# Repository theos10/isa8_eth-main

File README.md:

# ISA 8-Bit Ethernet Controller Low Profile
ISA 8-Bit Ethernet Network Interface Controller

## Introduction
ISA 8-Bit Ethernet Controller is an open source network interface controller (NIC) card, designed specifically to be used in computers with 8-bit only ISA (aka XT) bus, such as IBM* PC, IBM* PC XT, various PC/XT compatibles, for example [Micro 8088](https://github.com/skiselev/micro_8088) system. It is based on Realtek RTL8019 ethernet controller and is NE2000-compatible.

## Revision
Upgrade of the PCP to Low Profile by FOURNIER Ghislain.
Allows the card to be used in an Olivetti M19.
* Removal of the memory expansion connector MEM_EXT.
* Removal of the EPROM holder.
* Removal of the ROM address selection switches SW4.
* Removal and replacement of the RN3 and RN4 resistor network with an R4 SMD resistor.

## Specifications
* ISA 8-bit interface (62 pin / card edge)
* NE2000 compatible
  * Note: Popular Crynwr NE2000 pocket driver does not support NE2000 in 8-bit slots. Please use the [patched driver](software/driver/) instead
* Supports configuration using switches, jumperless configuration using [RSET8019](software/RSET8019/) utility or PnP
  * Uses DIP switches instead of jumpers for reliability and ease of configuration
* Boot ROM support
  * Socket supports 512 KiB Flash ROM, such as SST/Microchip 39SF040
  * Can be configured in 16 KiB, 32 KiB, 64 KiB, or page mode. In page mode the entire 512 KiB are accessible through a 16 KiB window
  * Also compatible with other DIP 32-pin Flash ROMs, such as 128 KiB 39SF010A, and 256 KiB 39SF020, or similar
  * 40-pin memory extension connector allows connecting up to 4 MiB of memory that can be used in page mode

## Hardware Documentation

### Schematic and PCB Layout

[Schematic - Version 1.0](KiCad/ISA8_Ethernet-Schematic-1.0.pdf)

[PCB Layout - Version 1.0](KiCad/ISA8_Ethernet-Board-1.0.pdf)

### Building Instructions

#### Assemble the PCB

* Clean the PCB with alcohol
* Apply fluid flux to SMD components pads
* Solder U1 RTL8019 IC
* Solder R1 - R7 resistors and RN1 - RN4 resistor arrays
  * Note that RN1 - RN3 are only required if using DIP switches for configuration. They are not required for jumperless configuration
* Solder C1 - C8 ceramic capacitors
* Solder C9 and C10 tantalum capacitors
* Solder Y1 crystal
* Optional: Program U3 EEPROM. Make sure to use unique MAC address
  * Note: EEPROM can be programmed later using [PG8019](software/PG8019/) utility
* Solder U3 EEPROM
* Optional: Solder SW1 - SW4 DIP switches and U2 IC socket
* Solder J1 Ethernet jack with integrated magentics
* Clean the remaining flux with alcohol

#### Program EEPROM

If EEPROM has not been programmed prior to assembly, now it is a good time to do so.
The U3 EEPROM contains the following configuration for the RTL8019AS chip:
* MAC address
* ISA resources for jumperless configuration
  * Base I/O address
  * IRQ number
  * Boot ROM mode, size, and base memory address
* Other ethernet controller confirguration - medium type, full duplex, LEDs function, power management settings
* Product ID (not normally used, although some vendor specific drivers might check for it)
* Plug and Play data
  * Vendor ID, serial number, PnP version, I/O, memory, and IRQ resources

This information can be programmed using [PG8019](software/PG8019/) utility. The 8019AS.CFG file contains the recommended configuration. Make sure to edit it, and update the MAC address and the serial number. Note that the MAC address is given in the Big-endian format (that is the last byte has the least significant value), while the serial number is given in Little-endian format (that is the first byte has the least significant value). 

A few notes about using PG8019:
* Make sure that your system has 0x300-0x31F I/O addresses available regardless of the Ethernet controller addresses specified in 8019AS.CFG. Note that XT-IDE and XT-CF-Lite frequently use this I/O range. In case you have such a card, you can either temporarily remove it from your system, boot and run PG8019 from a floppy disk, or switch your XT-IDE or XT-CF-Lite to a different address. In the latter case you'll need to update the XT IDE BIOS configuration
* Make sure that your system boots in real mode (no EMM386), or anything else that might interfer with the card. Ideally boot your system without any drivers loaded at all, for example, in later MS-DOS versions it is possible to bypass CONFIG.SYS and AUTOEXEC.BAT by hitting F5 key at the boot time
* After EEPROM has been programmed successfully, the PG8019 utility will print the MAC address, also, it will automatically increment the MAC address and the serial number in 8019AS.CFG, which is useful when programming multiple cards

[Openmoko Inc.](https://github.com/skiselev/openmoko-usb-oui) has generously allocated [00-1F-11-02-60-00 - 00-1F-11-02-7F-FF](https://github.com/skiselev/openmoko-usb-oui/blob/master/ieee_oui.psv) MAC addresses range for ISA 8-Bit Ethernet controller project. You can use MAC addresses from this range for your build, as long as you are using this design. Please apply for a different range if you're redesigning the board or re-using this Ethernet controller design in your own project. I ask you not to use 00-1F-11-02-60-00 - 00-1F-11-02-63-FF range (first 1024 addresses). I am using this range for the cards that I build.

#### Test Ethernet Controller

* Connect Ethernet cable. Make sure that the green "Link" LED lights up
* Use mTCP to test the controller
  * DHCP to obtain IP address
  * FTP or HTGET to download a file

### Switches and Connectors

#### SW1 - CONFIG
This switch block sets the configuration mode

Configuration Mode    | Switch Position
--------------------- | ------------------------
Jumperless / RSET8019 | SW1.1 = OFF, SW1.2 = OFF
Switches              | SW1.1 = ON, SW1.2 = OFF
PnP                   | SW1.1 = OFF, SW1.2 = ON

#### SW2 - IRQ
This switch block, when the card is in the **Switches** configuration mode, sets the Ethernet controller IRQ

IRQ                             | Switch Position
------------------------------- | ------------------------
IRQ2 (on PC/XT) or IRQ9 (on AT) | SW2.1 = OFF, SW2.2 = OFF
IRQ3                            | SW2.1 = ON, SW2.2 = OFF
IRQ4                            | SW2.1 = OFF, SW2.2 = ON
IRQ5                            | SW2.1 = ON, SW2.2 = ON

#### SW3 - IO_ADDR
This switch block, when the card is in the **Switches** configuration mode, sets the Ethernet controller I/O address

I/O Address | SW3.1 | SW3.2 | SW3.3 | SW3.4
----------- | ----- | ----- | ------| -----
0x200       | OFF   | OFF   | ON    | OFF
0x220       | ON    | OFF   | ON    | OFF
0x240       | OFF   | ON    | ON    | OFF
0x260       | ON    | ON    | ON    | OFF
0x280       | OFF   | OFF   | ON    | ON
0x2A0       | ON    | OFF   | ON    | ON
0x2C0       | OFF   | ON    | ON    | ON
0x2E0       | ON    | ON    | ON    | ON
0x300       | OFF   | OFF   | OFF   | OFF
0x320       | ON    | OFF   | OFF   | OFF
0x340       | OFF   | ON    | OFF   | OFF
0x360       | ON    | ON    | OFF   | OFF
0x380       | OFF   | OFF   | OFF   | ON
0x3A0       | ON    | OFF   | OFF   | ON
0x3C0       | OFF   | ON    | OFF   | ON
0x3E0       | ON    | ON    | OFF   | ON

#### J1 - Ethernet Connector

### Bill of Materials - Version 1.0

[ISA 8-bit Ethernet project on Mouser.com](https://www.mouser.com/ProjectManager/ProjectDetail.aspx?AccessID=6373f65c4a) - View and order all components except of the PCB and the Realtek RTL8019 IC.

[ISA 8-bit Ethernet project on OSH Park](https://oshpark.com/shared_projects/OBud8i6u) - View and order the PCB.

Component type     | Reference | Description                           | Quantity | Possible sources and notes 
------------------ | --------- | ------------------------------------- | -------- | --------------------------
PCB                |           | ISA 8-bit Ethernet PCB - Version 1.0  | 1        | Buy from my Tindie store: [ISA 8-bit Ethernet PCB, and optionally a preprogrammed EEPROM](https://www.tindie.com/products/weird/isa8-eth-pcb), or order from a PCB manufacturer of your choice using provided Gerber or KiCad files
Integrated Circuit | U1        | Realtek RTL8019AS Ethernet Controller | 1        | Authorized Realtek distributors or eBay
Integrated Circuit | U3        | 93C46 - 1 Kbit EEPROM, 4 pin SOIC     | 1        | Mouser [511-M93C46-WMN6TP](https://www.mouser.com/ProductDetail/511-M93C46-WMN6TP)
Quartz Crystal     | Y1        | 20 MHz, 18pF, HC-49U                  | 1        | Mouser [774-ATS200C](https://www.mouser.com/ProductDetail/774-ATS200C)
Ethernet Jack      | J1        | Amphenol RJMG1BD3B8K1ANR - Ethernet jack with magnetics | 1 | Mouser [523-RJMG1BD3B8K1ANR](https://www.mouser.com/ProductDetail/523-RJMG1BD3B8K1ANR)
DIP Switch         | SW1, SW2  | DIP switch, 2 position, SPST          | 2        | Mouser [774-2102MS](https://www.mouser.com/ProductDetail/774-2102MS)
DIP Switch         | SW3       | DIP switch, 4 position, SPST          | 1        | Mouser [774-2104MS](https://www.mouser.com/ProductDetail/774-2104MS)
Capacitor          | C1, C2    | 10pF MLCC Capacitor, 0603 SMT         | 2        | Mouser [77-VJ0603A100JXACBC](https://www.mouser.com/ProductDetail/77-VJ0603A100JXACBC)
Capacitor          | C3, C4    | 0.01uF MLCC Capacitor, 0603 SMT       | 2        | Mouser [77-VJ0603Y103JXACBC](https://www.mouser.com/ProductDetail/77-VJ0603Y103JXACBC)
Capacitor          | C5 - C8   | 0.1uF MLCC Capacitor, 0603 SMT        | 4        | Mouser [77-VJ0603Y104JXJPBC](https://www.mouser.com/ProductDetail/77-VJ0603Y104JXJPBC)
Capacitor          | C9, C10   | 22uF Tantalum Capacitor, 1210 SMT     | 2        | Mouser [581-TAJB226K016TNJ](https://www.mouser.com/ProductDetail/581-TAJB226K016TNJ)
Resistor           | R1        | 200 Ohm Resistor, 0603 SMT            | 1        | Mouser [603-RC0603FR-13200RL](https://www.mouser.com/ProductDetail/603-RC0603FR-13200RL)
Resistor           | R2, R3    | 470 Ohm Resistor, 0603 SMT            | 2        | Mouser [603-RC0603FR-13470RL](https://www.mouser.com/ProductDetail/603-RC0603FR-13470RL)
Resistor           | R4        | 10 kOhm Resistor, 0603 SMT            | 1        | Mouser [603-RC0603FR-1310KL](https://www.mouser.fr/ProductDetail/YAGEO/RC0603FR-1310KL)
Resistor           | R6        | 27 kOhm Resistor, 0603 SMT            | 1        | Mouser [603-RC0603FR-1327KL](https://www.mouser.com/ProductDetail/603-RC0603FR-1327KL)
Resistor           | R7        | 1 MOhm Resistor, 0603 SMT             | 1        | Mouser [603-RC0603FR-131ML](https://www.mouser.com/ProductDetail/603-RC0603FR-131ML)
Resistor Array     | RN1 - RN2 | 10 kOhm x 4 Resistor Array, 0603 SMT  | 2        | Mouser [667-EXB-38V103JV](https://www.mouser.com/ProductDetail/667-EXB-38V103JV)

## Reference Information

### Realtek RTL8019AS EEPROM Content

The Realtek RTL8019AS uses 93C46 - 1Kbit / 128 bytes EEPROM to store the configuration. The EEPROM is accessed using 16-bit word mode, with data being stored in Big-endian format. This means that the bytes should be swapped when the EEPROM content is accessed on an x86 system.

Address      | Size | Content                                | Default Configuration for ISA 8-Bit Ethernet
-------------|------|----------------------------------------|---------------------------------------------
0x00 - 0x03  | 4    | CONFIG1, CONFIG2, CONFIG3, CONFIG4     |
0x00         | 1    | CONFIG1                                | 0x07
0x01         | 1    | CONFIG2                                | 0x00
0x02         | 1    | CONFIG3                                | 0xD0
0x03         | 1    | CONFIG4                                | 0x01
0x04 - 0x09  | 6    | Ethernet ID (MAC Address)              | 0x00 0x1F 0x11 0x02 0x70 0x00
0x0A - 0x11  | 8    | Product ID                             | 0x49 0x53 0x41 0x38 0x45 0x54 0x48 0x20
0x12 - 0x1A  | 9    | PnP header                             | 
0x12 - 0x15  | 4    | Vendor ID (0-3)                        |  
0x12 - 0x13  | 2    | Vendor ID - compressed ASCII (00000=A) | 0x4A 0x8C - 0 10010=R 10100=T 01100=L
0x14 - 0x15  | 2    | Vendor ID - product number             | 0x80 0x19 - 8019
0x16 - 0x19  | 4    | Serial Number (0-3)                    | 0x00 0x10 0x00 0x00
0x1A         | 1    | Checksum                               | ?
0x1B - 0x7F  | 101  | PnP Resource Data                      | 
0x1B - 0x1D  | 3    | PnP Version Number                     |
0x1B         | 1    | Item byte                              | 0x0A
0x1C         | 1    | PnP Version                            | 0x10
0x1D         | 1    | Vendor Version                         | 0x10
0x1E - 0x3B  | 37   | ANSI Identifier String                 | 
0x1E         | 1    | Item byte                              | 0x82
0x1F         | 1    | Length, bits 7-0                       | 0x24
0x20         | 1    | Length, bits 15-8                      | 0x00
0x21 - 0x44  | 36   | Identifier String                      | "ISA 8-Bit Plug & Play Ethernet Card", 0x00
0x45 - 0x4B  | 7    | Logical Device ID                      |
0x45         | 1    | Item byte                              | 0x16
0x46 - 0x49  | 4    | Logical Device ID 0-3                  | 0x00 0x00 0x80 0x19
0x4A         | 1    | Flag 0                                 | 0x02 (Boot ROM disabled) or 0x03 (Boot ROM enabled)
0x4B         | 1    | Flag 1                                 | 0x00
0x4C - 0x50  | 5    | Compatible Device ID (NE2000 compatible) |
0x4C         | 1    | Item byte                              | 0x1C
0x4D - 0x50  | 4    | Compatible ID                          | 0x41 0xD0 0x80 0xD6
0x51 - 0x58  | 8    | I/O Format                             |
0x51         | 1    | Item byte                              | 0x47
0x52         | 1    | I/O Information                        | 0x00
0x53         | 1    | Minimal I/O base, bits 7-0             | 0x20
0x54         | 1    | Minimal I/O base, bits 15-8            | 0x02
0x55         | 1    | Maximal I/O base, bits 7-0             | 0x80
0x56         | 1    | Maximal I/O base, bits 15-8            | 0x03
0x57         | 1    | Base alignment                         | 0x20
0x58         | 1    | Range length                           | 0x20
0x59 - 0x5C  | 4    | IRQ Format                             |
0x59         | 1    | Item byte                              | 0x23 - Small item name = 0x04 (IRQ), Length = 3
0x5A         | 1    | IRQ mask bits 7-0                      | 0x3C - IRQ 0-7 mask - IRQ5, IRQ4, IRQ3, IRQ2
0x5B         | 1    | IRQ mask bits 15-8                     | 0x02 - IRQ 8-15 mask - IRQ9 (note: IRQ9 is the same as IRQ2, others are not available on an 8-bit slot)
0x5C         | 1    | IRQ information                        | 0x01 - High true edge sensitive
0x5D - 0x6A  | 12   | Memory Format (optional)               | 64 KiB Boot ROM (16 KiB Boot ROM)
0x5D         | 1    | Item byte                              | 0x81
0x5E         | 1    | Length, bits 7-0                       | 0x09
0x5F         | 1    | Length, bits 15-8                      | 0x00
0x60         | 1    | Memory information                     | 0x40
0x61         | 1    | Minimal base, bits 15-8                | 0x00
0x62         | 1    | Minimal base, bits 24-16               | 0x0C
0x63         | 1    | Maximal base, bits 7-0                 | 0x00 (0xC0 for 16 KiB)
0x64         | 1    | Maximal base, bits 15-8                | 0x0D
0x65         | 1    | Base alignment, bits 7-0               | 0x00
0x66         | 1    | Base alignment, bits 15-8              | 0x00 (0x40 for 16 KiB)
0x67         | 1    | Range length bits 15-8                 | 0x00 (0x40 for 16 KiB)
0x68         | 1    | Range length bits 24-16                | 0x01 (0x00 for 16 KiB)
0x69 - 0x6A  | 2    | End Tag                                |
0x6B         | 1    | Item byte                              | 0x79
0x6C         | 1    | Checksum of the resource data          | 0x1F
0x6D-0x7F    | ?    | Unused space                           | 0xFF

## Red Tape

### Licensing

ISA 8-bit Ethernet is an open source hardware project certified by [Open Source Hardware Association](https://www.oshwa.org/), certification UID is [US002001](https://certification.oshwa.org/us002001.html). The hardware design itself, including schematic and PCB layout design files are licensed under the strongly-reciprocal variant of [CERN Open Hardware Licence version 2](license-cern_ohl_s_v2.txt). The NE2000 driver code is licensed under [GNU General Public License v2](license-gpl-2.0.txt). Documentation, including this file, is licensed under the [Creative Commons Attribution-ShareAlike 4.0 International License](license-cc-by-sa-4.0.txt).

KiCad symbols and modules used in this project are available in [my KiCad library](https://github.com/skiselev/my_kicad_library) repository

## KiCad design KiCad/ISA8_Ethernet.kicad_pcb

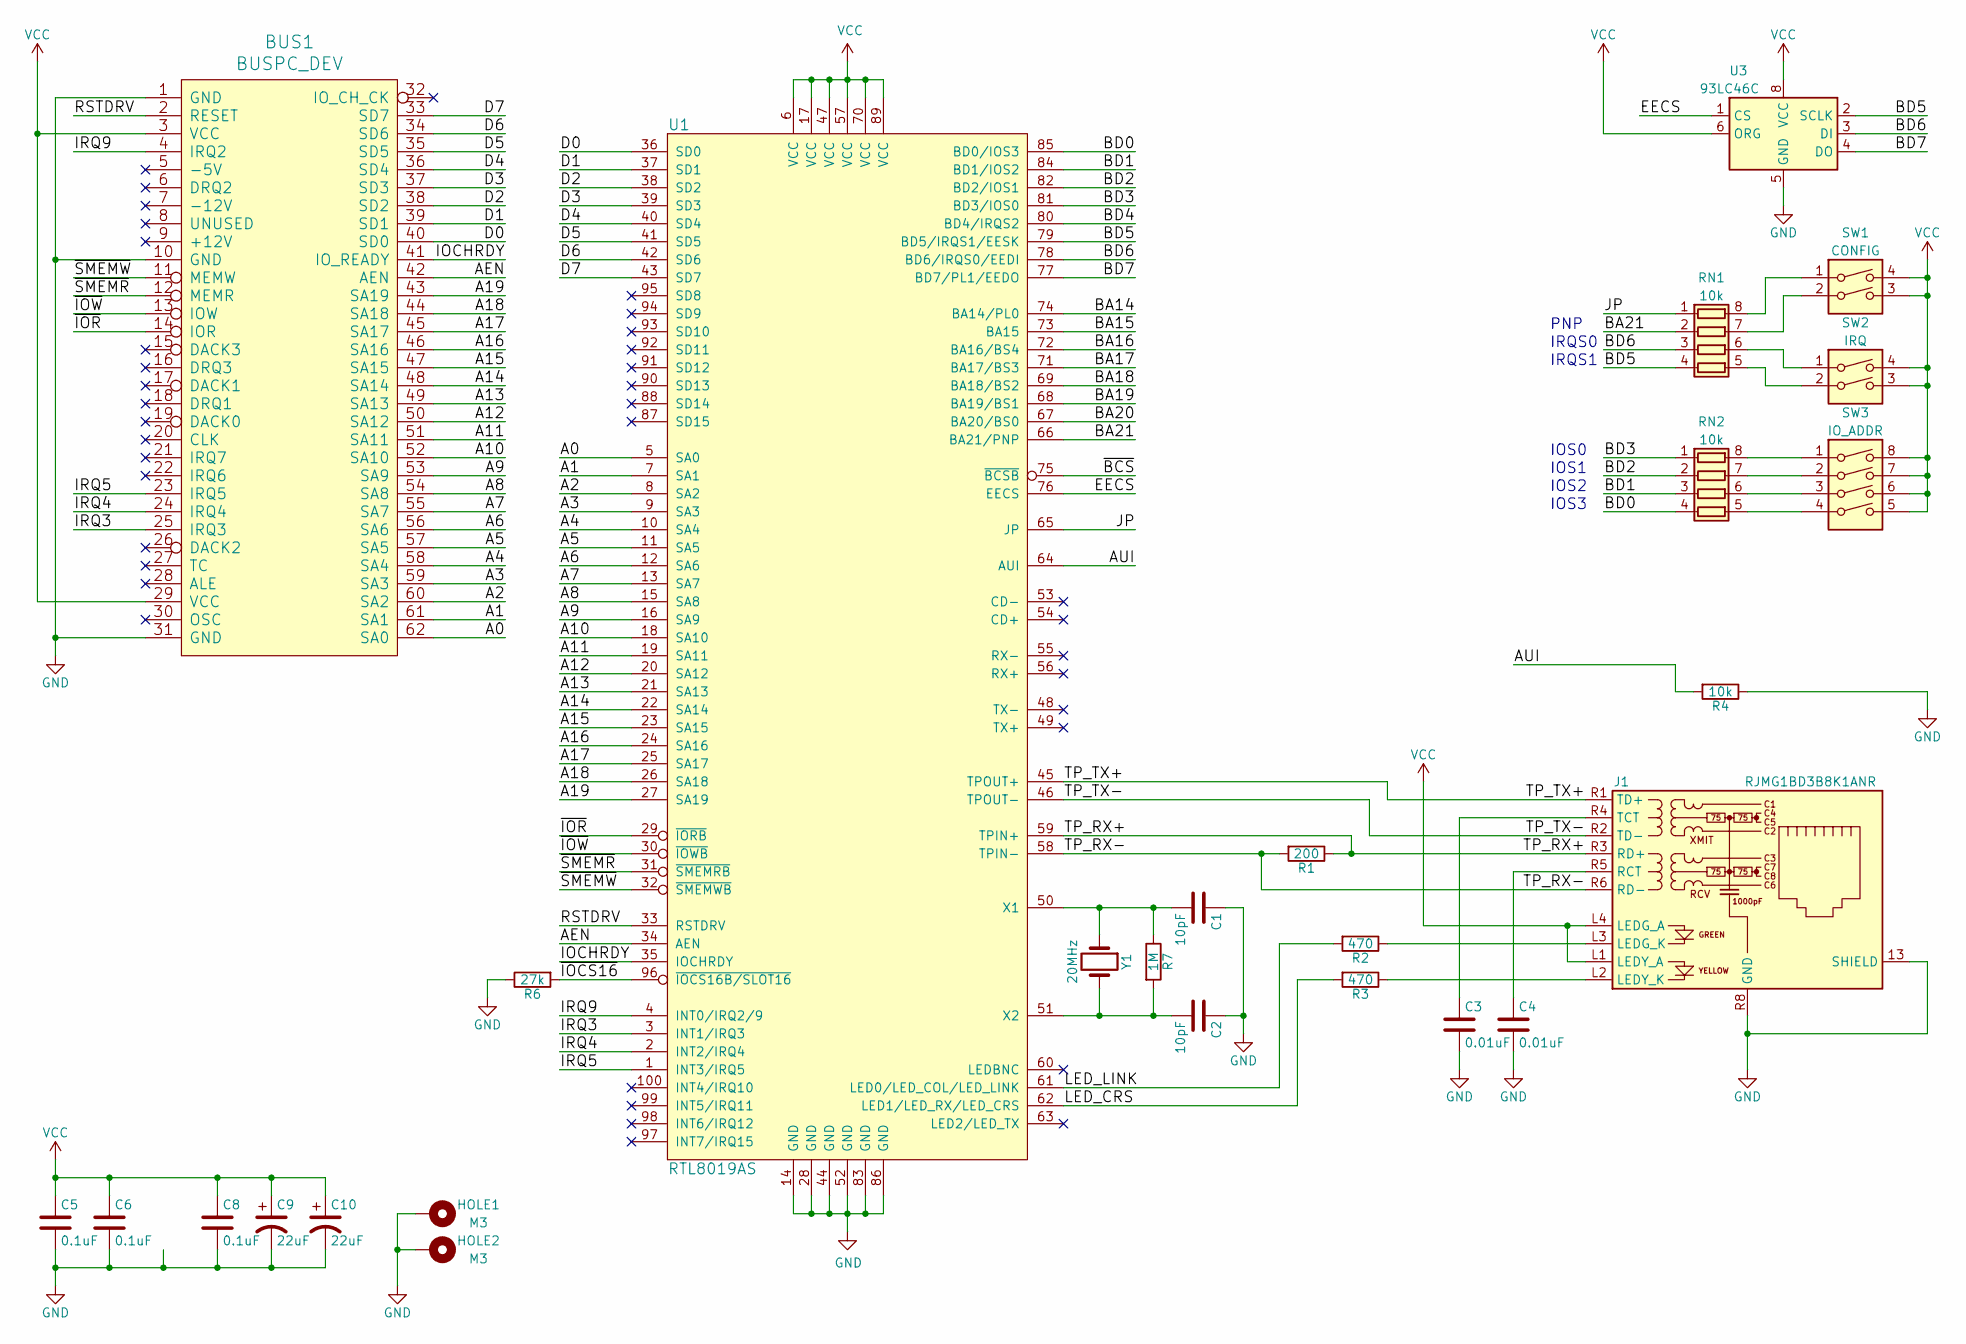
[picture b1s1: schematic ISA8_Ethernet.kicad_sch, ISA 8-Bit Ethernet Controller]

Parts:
BUS1: BUSPC_DEV; Conn_Edge_PCB_ISA8
C1, C2: 10pF; C_0603_1608Metric_Pad1.08x0.95mm_HandSolder
C3, C4: 0.01uF; C_0603_1608Metric_Pad1.08x0.95mm_HandSolder
C5, C6, C8: 0.1uF; C_0603_1608Metric_Pad1.08x0.95mm_HandSolder
C9, C10: 22uF; CP_EIA-3528-15_AVX-H_Pad1.50x2.35mm_HandSolder
HOLE1, HOLE2: M3; MountingHole_3.2mm_M3_Pad_Via
J1: RJMG1BD3B8K1ANR; RJ45_Amphenol_RJMG1BD3B8K1ANR
R1: 200; R_0603_1608Metric_Pad0.98x0.95mm_HandSolder
R2, R3: 470; R_0603_1608Metric_Pad0.98x0.95mm_HandSolder
R4: 10k; R_0603_1608Metric_Pad0.98x0.95mm_HandSolder
R6: 27k; R_0603_1608Metric_Pad0.98x0.95mm_HandSolder
R7: 1M; R_0603_1608Metric_Pad0.98x0.95mm_HandSolder
RN1, RN2: 10k; R_Array_Convex_4x0603
SW1: CONFIG; Switch_DIP_2_Positions
SW2: IRQ; Switch_DIP_2_Positions
SW3: IO_ADDR; Switch_DIP_4_Positions
U1: RTL8019AS; IC_PQFP-100_14x20mm_P0.65mm_Hand_Soldering
U3: 93LC46C; SO-8_3.9x4.9mm_P1.27mm
Y1: 20MHz; Crystal_HC-49U_Vert

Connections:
/A0: BUS1.62 (SA0), U1.5 (SA0)
/A1: BUS1.61 (SA1), U1.7 (SA1)
/A2: BUS1.60 (SA2), U1.8 (SA2)
/A3: BUS1.59 (SA3), U1.9 (SA3)
/A4: BUS1.58 (SA4), U1.10 (SA4)
/A5: BUS1.57 (SA5), U1.11 (SA5)
/A6: BUS1.56 (SA6), U1.12 (SA6)
/A7: BUS1.55 (SA7), U1.13 (SA7)
/A8: BUS1.54 (SA8), U1.15 (SA8)
/A9: BUS1.53 (SA9), U1.16 (SA9)
/A10: BUS1.52 (SA10), U1.18 (SA10)
/A11: BUS1.51 (SA11), U1.19 (SA11)
/A12: BUS1.50 (SA12), U1.20 (SA12)
/A13: BUS1.49 (SA13), U1.21 (SA13)
/A14: BUS1.48 (SA14), U1.22 (SA14)
/A15: BUS1.47 (SA15), U1.23 (SA15)
/A16: BUS1.46 (SA16), U1.24 (SA16)
/A17: BUS1.45 (SA17), U1.25 (SA17)
/A18: BUS1.44 (SA18), U1.26 (SA18)
/A19: BUS1.43 (SA19), U1.27 (SA19)
/AEN: BUS1.42 (AEN), U1.34 (AEN)
/AUI: R4.2, U1.64 (AUI)
/BA14: U1.74 (BA14/PL0)
/BA15: U1.73 (BA15)
/BA16: U1.72 (BA16/BS4)
/BA17: U1.71 (BA17/BS3)
/BA18: U1.69 (BA18/BS2)
/BA19: U1.68 (BA19/BS1)
/BA20: U1.67 (BA20/BS0)
/BA21: RN1.2 (R2.1), U1.66 (BA21/PNP)
/BD0: RN2.4 (R4.1), U1.85 (BD0/IOS3)
/BD1: RN2.3 (R3.1), U1.84 (BD1/IOS2)
/BD2: RN2.2 (R2.1), U1.82 (BD2/IOS1)
/BD3: RN2.1 (R1.1), U1.81 (BD3/IOS0)
/BD4: U1.80 (BD4/IRQS2)
/BD5: RN1.4 (R4.1), U1.79 (BD5/IRQS1/EESK), U3.2 (SCLK)
/BD6: RN1.3 (R3.1), U1.78 (BD6/IRQS0/EEDI), U3.3 (DI)
/BD7: U1.77 (BD7/PL1/EEDO), U3.4 (DO)
/D0: BUS1.40 (SD0), U1.36 (SD0)
/D1: BUS1.39 (SD1), U1.37 (SD1)
/D2: BUS1.38 (SD2), U1.38 (SD2)
/D3: BUS1.37 (SD3), U1.39 (SD3)
/D4: BUS1.36 (SD4), U1.40 (SD4)
/D5: BUS1.35 (SD5), U1.41 (SD5)
/D6: BUS1.34 (SD6), U1.42 (SD6)
/D7: BUS1.33 (SD7), U1.43 (SD7)
/EECS: U1.76 (EECS), U3.1 (CS)
/IOCHRDY: BUS1.41 (IO_READY), U1.35 (IOCHRDY)
/IRQ3: BUS1.25 (IRQ3), U1.3 (INT1/IRQ3)
/IRQ4: BUS1.24 (IRQ4), U1.2 (INT2/IRQ4)
/IRQ5: BUS1.23 (IRQ5), U1.1 (INT3/IRQ5)
/IRQ9: BUS1.4 (IRQ2), U1.4 (INT0/IRQ2/9)
/JP: RN1.1 (R1.1), U1.65 (JP)
/LED_CRS: R3.2, U1.62 (LED1/LED_RX/LED_CRS)
/LED_LINK: R2.2, U1.61 (LED0/LED_COL/LED_LINK)
/RSTDRV: BUS1.2 (RESET), U1.33 (RSTDRV)
/TP_RX+: J1.R3 (RD+), R1.1, U1.59 (TPIN+)
/TP_RX-: J1.R6 (RD-), R1.2, U1.58 (TPIN-)
/TP_TX+: J1.R1 (TD+), U1.45 (TPOUT+)
/TP_TX-: J1.R2 (TD-), U1.46 (TPOUT-)
/~BCS: U1.75 (~BCSB)
/~IOCS16: R6.2, U1.96 (~IOCS16B/SLOT16)
/~IOR: BUS1.14 (IOR), U1.29 (~IORB)
/~IOW: BUS1.13 (IOW), U1.30 (~IOWB)
/~SMEMR: BUS1.12 (MEMR), U1.31 (~SMEMRB)
/~SMEMW: BUS1.11 (MEMW), U1.32 (~SMEMWB)
GND: BUS1.1 (GND), BUS1.10 (GND), BUS1.31 (GND), C1.1, C2.1, C3.2, C4.2, C5.2, C6.2, C8.2, C9.2, C10.2, HOLE1.1, HOLE2.1, J1.13 (SHIELD), J1.R8 (GND), R4.1, R6.1, U1.14 (GND), U1.28 (GND), U1.44 (GND), U1.52 (GND), U1.83 (GND), U1.86 (GND), U3.5 (GND)
unnamed: J1.L3 (LEDG_K), R2.1
unnamed: J1.L2 (LEDY_K), R3.1
unnamed: C4.1, J1.R5 (RCT)
unnamed: C3.1, J1.R4 (TCT)
unnamed: RN1.8 (R1.2), SW1.1
unnamed: RN1.7 (R2.2), SW1.2
unnamed: RN1.6 (R3.2), SW2.1
unnamed: RN1.5 (R4.2), SW2.2
unnamed: RN2.8 (R1.2), SW3.1
unnamed: RN2.7 (R2.2), SW3.2
unnamed: RN2.6 (R3.2), SW3.3
unnamed: RN2.5 (R4.2), SW3.4
unnamed: C1.2, R7.1, U1.50 (X1), Y1.1
unnamed: C2.2, R7.2, U1.51 (X2), Y1.2
VCC: BUS1.3 (VCC), BUS1.29 (VCC), C5.1, C6.1, C8.1, C9.1, C10.1, J1.L1 (LEDY_A), J1.L4 (LEDG_A), SW1.3, SW1.4, SW2.3, SW2.4, SW3.5, SW3.6, SW3.7, SW3.8, U1.6 (VCC), U1.17 (VCC), U1.47 (VCC), U1.57 (VCC), U1.70 (VCC), U1.89 (VCC), U3.6 (ORG), U3.8 (VCC)

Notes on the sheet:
IRQS1
PNP
IOS1
IOS2
IOS0
IOS3
IRQS0

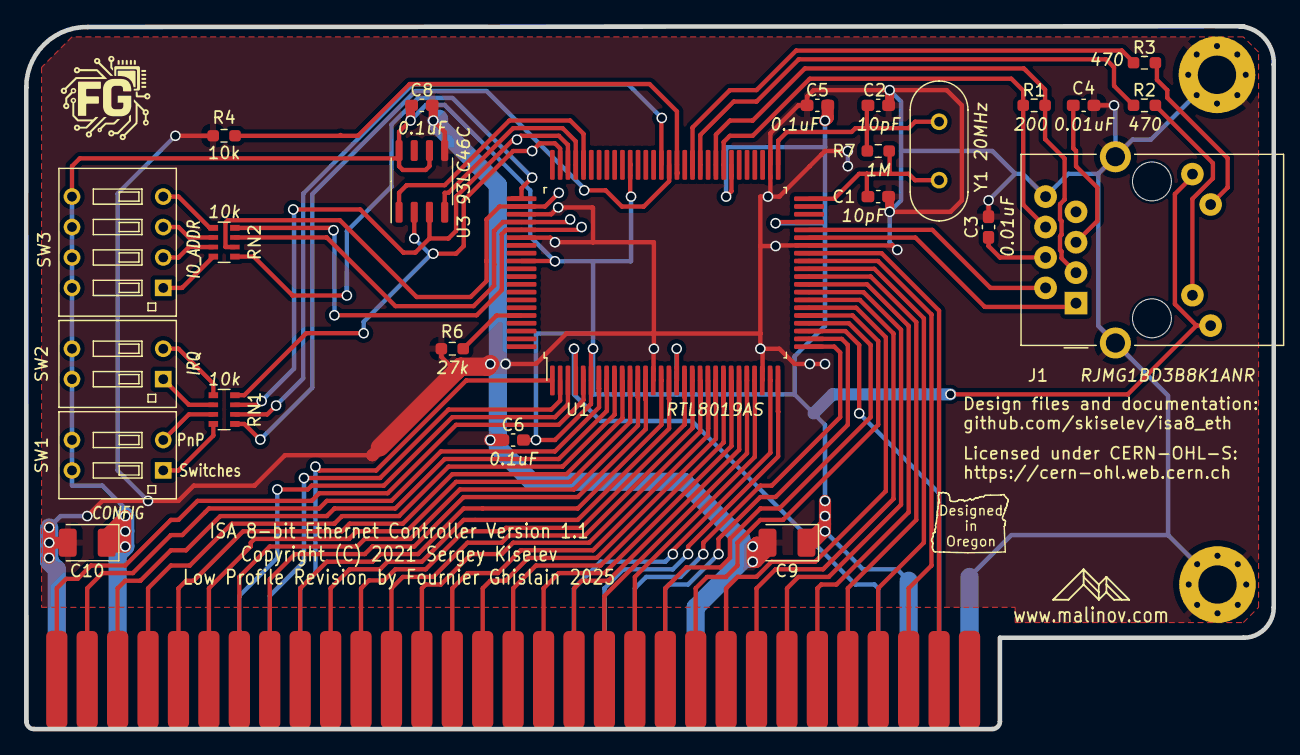
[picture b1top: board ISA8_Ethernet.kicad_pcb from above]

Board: 2 copper layers, 104.1 x 58.7 mm, 27 parts (0 on the bottom side), 73 nets.

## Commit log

2025-07-06 Add PCB Picture

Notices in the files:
README.md:
Licensing:
ISA 8-bit Ethernet is an open source hardware project certified by [Open Source Hardware Association](https://www.oshwa.org/), certification UID is [US002001](https://certification.oshwa.org/us002001.html). The hardware design itself, including schematic and PCB layout design files are licensed under the strongly-reciprocal variant of [CERN Open Hardware Licence version 2](license-cern_ohl_s_v2.txt). The NE2000 driver code is licensed under [GNU General Public License v2](license-gpl-2.0.txt). Documentation, including this file, is licensed under the [Creative Commons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
